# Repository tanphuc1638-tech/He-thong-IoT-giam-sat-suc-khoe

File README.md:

# Health Dashboard - Frontend (Next.js + R3F + MQTT + Firebase)

## 1. Cau truc thu muc

```
health-dashboard/
├── mosquitto/
│   └── mosquitto.conf          # Cau hinh broker (TCP 1883 + WebSocket 9001)
├── src/
│   ├── app/
│   │   ├── layout.tsx          # Root layout, nap font Inter + Orbitron
│   │   ├── page.tsx            # Trang chinh - ghep toan bo component
│   │   └── globals.css         # Tailwind directives + utility glow
│   ├── components/
│   │   ├── Heart3D.tsx         # Quan tim 3D (R3F) dap theo BPM
│   │   ├── MetricsPanel.tsx    # So BPM lon + goi SpO2Gauge
│   │   ├── SpO2Gauge.tsx       # Gauge vong tron SpO2 (SVG)
│   │   ├── AIDiagnosisCard.tsx # The chan doan AI, vien glow theo severity
│   │   ├── TrendChart.tsx      # Line chart Recharts, xu huong BPM
│   │   └── HistoryTable.tsx    # Bang 5 ban ghi gan nhat tu Firestore
│   ├── lib/
│   │   ├── mqttService.ts      # Hook useHealthMqtt() - ket noi WS toi Mosquitto
│   │   ├── firebase.ts         # Khoi tao Firebase + doc/ghi Firestore
│   │   └── theme.ts            # Anh xa status AI -> mau sac (severity)
│   └── types/
│       └── health.ts           # Kieu du lieu dung chung
├── package.json
├── tailwind.config.ts
├── tsconfig.json
├── postcss.config.js
├── next.config.js
└── .env.local.example
```

## 2. Cai dat

```bash
npm install
cp .env.local.example .env.local
# -> dien NEXT_PUBLIC_FIREBASE_* tu Firebase Console vao .env.local
```

> **Luu y ve Tailwind**: project nay dung Tailwind **v3** (file
> `tailwind.config.ts` + `@tailwind base/components/utilities` trong
> `globals.css`). Neu `npm install` keo ve Tailwind v4 do khong ghi ro
> version, cau hinh se khong chay dung - package.json da pin san
> `"tailwindcss": "^3.4.0"` nen chi can `npm install` binh thuong la du.

## 3. Cau hinh Mosquitto mo them WebSocket (port 9001)

Frontend chay trong trinh duyet KHONG the mo TCP socket thuan toi port 1883
nhu ESP32/Backend Python - bat buoc phai qua WebSocket. File
`mosquitto/mosquitto.conf` da chuan bi san 2 listener:

```
listener 1883
protocol mqtt

listener 9001
protocol websockets

allow_anonymous true
```

Chay Mosquitto voi file cau hinh nay (thay duong dan cho phu hop he dieu hanh):

```bash
mosquitto -c ./mosquitto/mosquitto.conf -v
```

`-v` de in log chi tiet, huu ich khi debug ket noi luc dau. Kiem tra thay 2
dong `Opening ipv4 listen socket on port 1883` va `...port 9001` la broker
da san sang cho ca ESP32/Backend lan Frontend.

## 4. Chay Frontend

```bash
npm run dev
```

Mo `http://localhost:3000`. Goc tren ben phai se hien "Da ket noi MQTT" khi
WebSocket toi Mosquitto thanh cong; sau do moi khi Backend Python publish
len topic `tdtu/health/ai_result`, toan bo dashboard (quan tim, so lieu,
chan doan, bieu do, lich su) se tu cap nhat realtime.

## 5. Firestore

Tao Firestore Database (Native mode) trong Firebase Console, khong can tao
truoc collection `health_records` - `saveHealthRecord()` trong
`lib/firebase.ts` se tu tao khi co ban ghi dau tien. Nho thiet lap Security
Rules phu hop truoc khi dua ra ngoai moi truong dev (mac dinh Firestore moi
tao o "test mode" se tu khoa ghi/doc sau 30 ngay).

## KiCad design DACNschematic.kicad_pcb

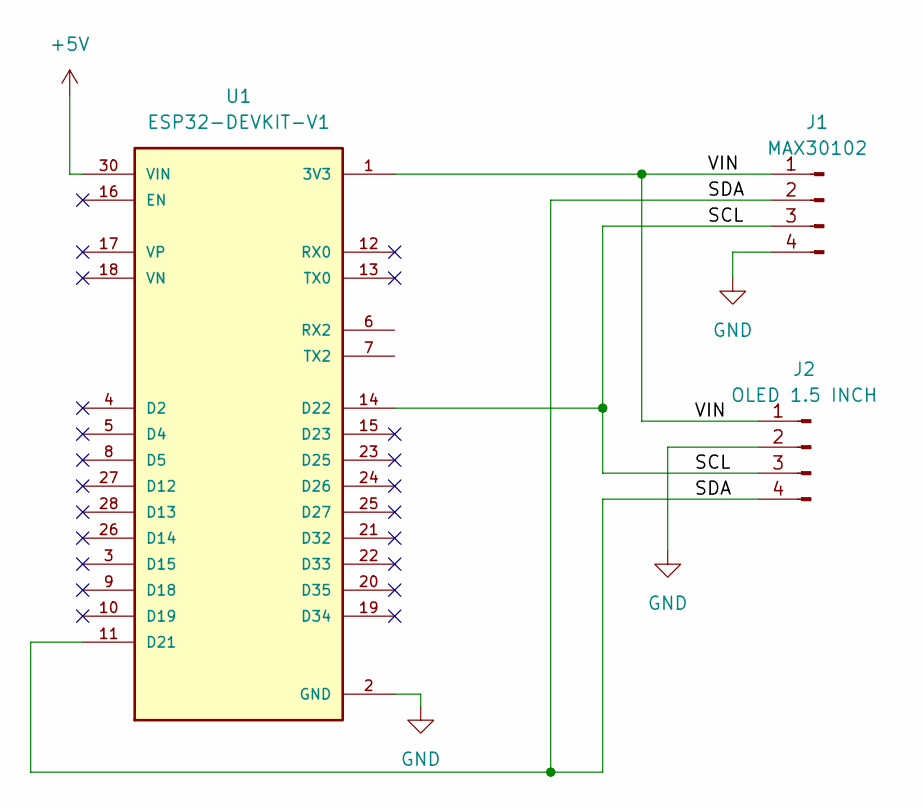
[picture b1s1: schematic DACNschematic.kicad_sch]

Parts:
J1: MAX30102; PinSocket_1x04_P2.54mm_Vertical
J2: OLED 1.5 INCH; PinSocket_1x04_P2.54mm_Vertical
U1: ESP32-DEVKIT-V1; MODULE_ESP32_DEVKIT_V1; PARTREV N/A

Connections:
+5V: U1.30 (VIN)
/RX: U1.7 (TX2)
/SCL: J1.3, J2.3, U1.14 (D22)
/SDA: J1.2, J2.4, U1.11 (D21)
/TX: U1.6 (RX2)
/VIN: J1.1, J2.1, U1.1 (3V3)
GND: J1.4, J2.2, U1.2 (GND), U1.29 (GND)

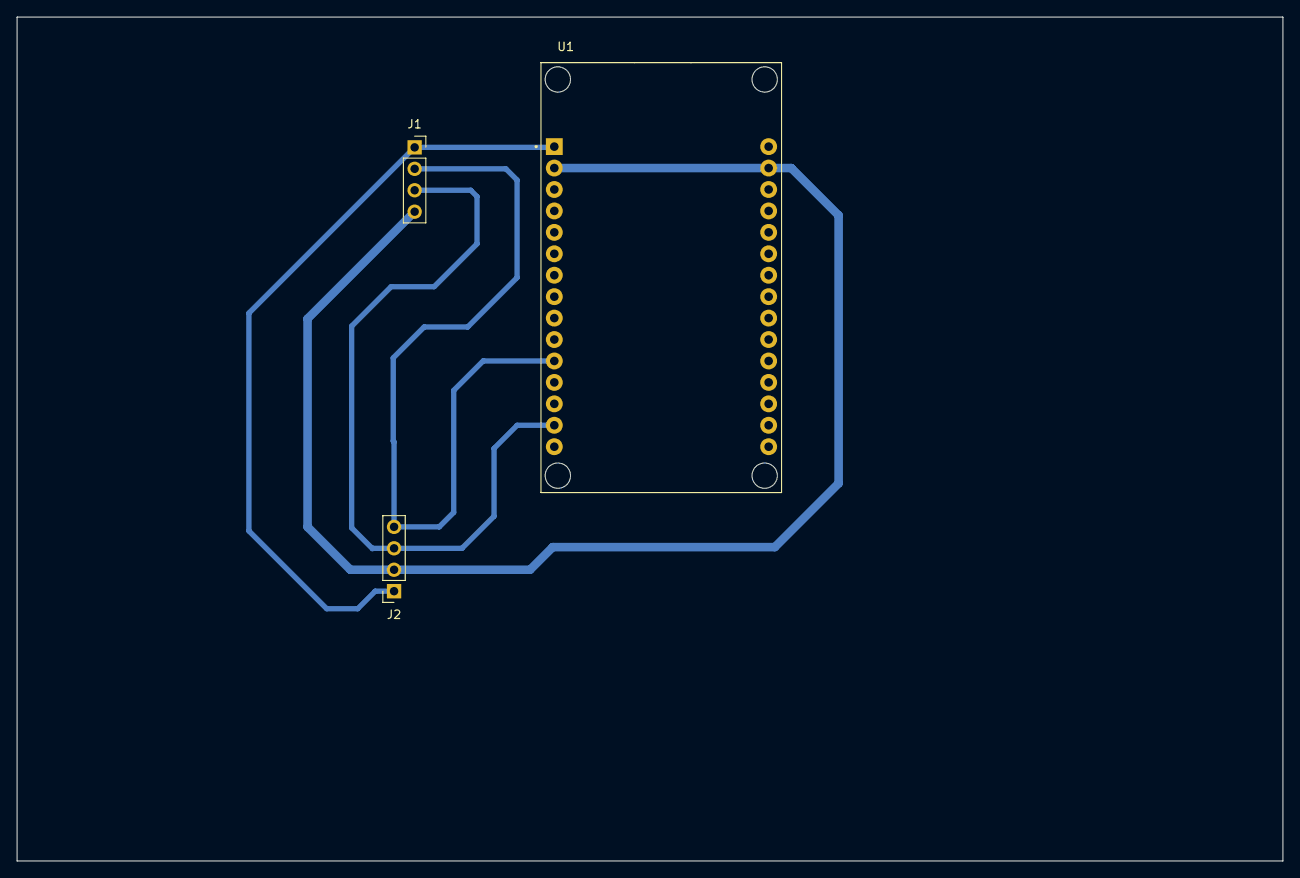
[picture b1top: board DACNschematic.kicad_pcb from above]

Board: 2 copper layers, 150.0 x 100.0 mm, 3 parts (0 on the bottom side), 4 nets.
